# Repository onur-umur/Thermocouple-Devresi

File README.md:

# Thermocouple-Devresi
Jet Motoru için thermocouple devresi

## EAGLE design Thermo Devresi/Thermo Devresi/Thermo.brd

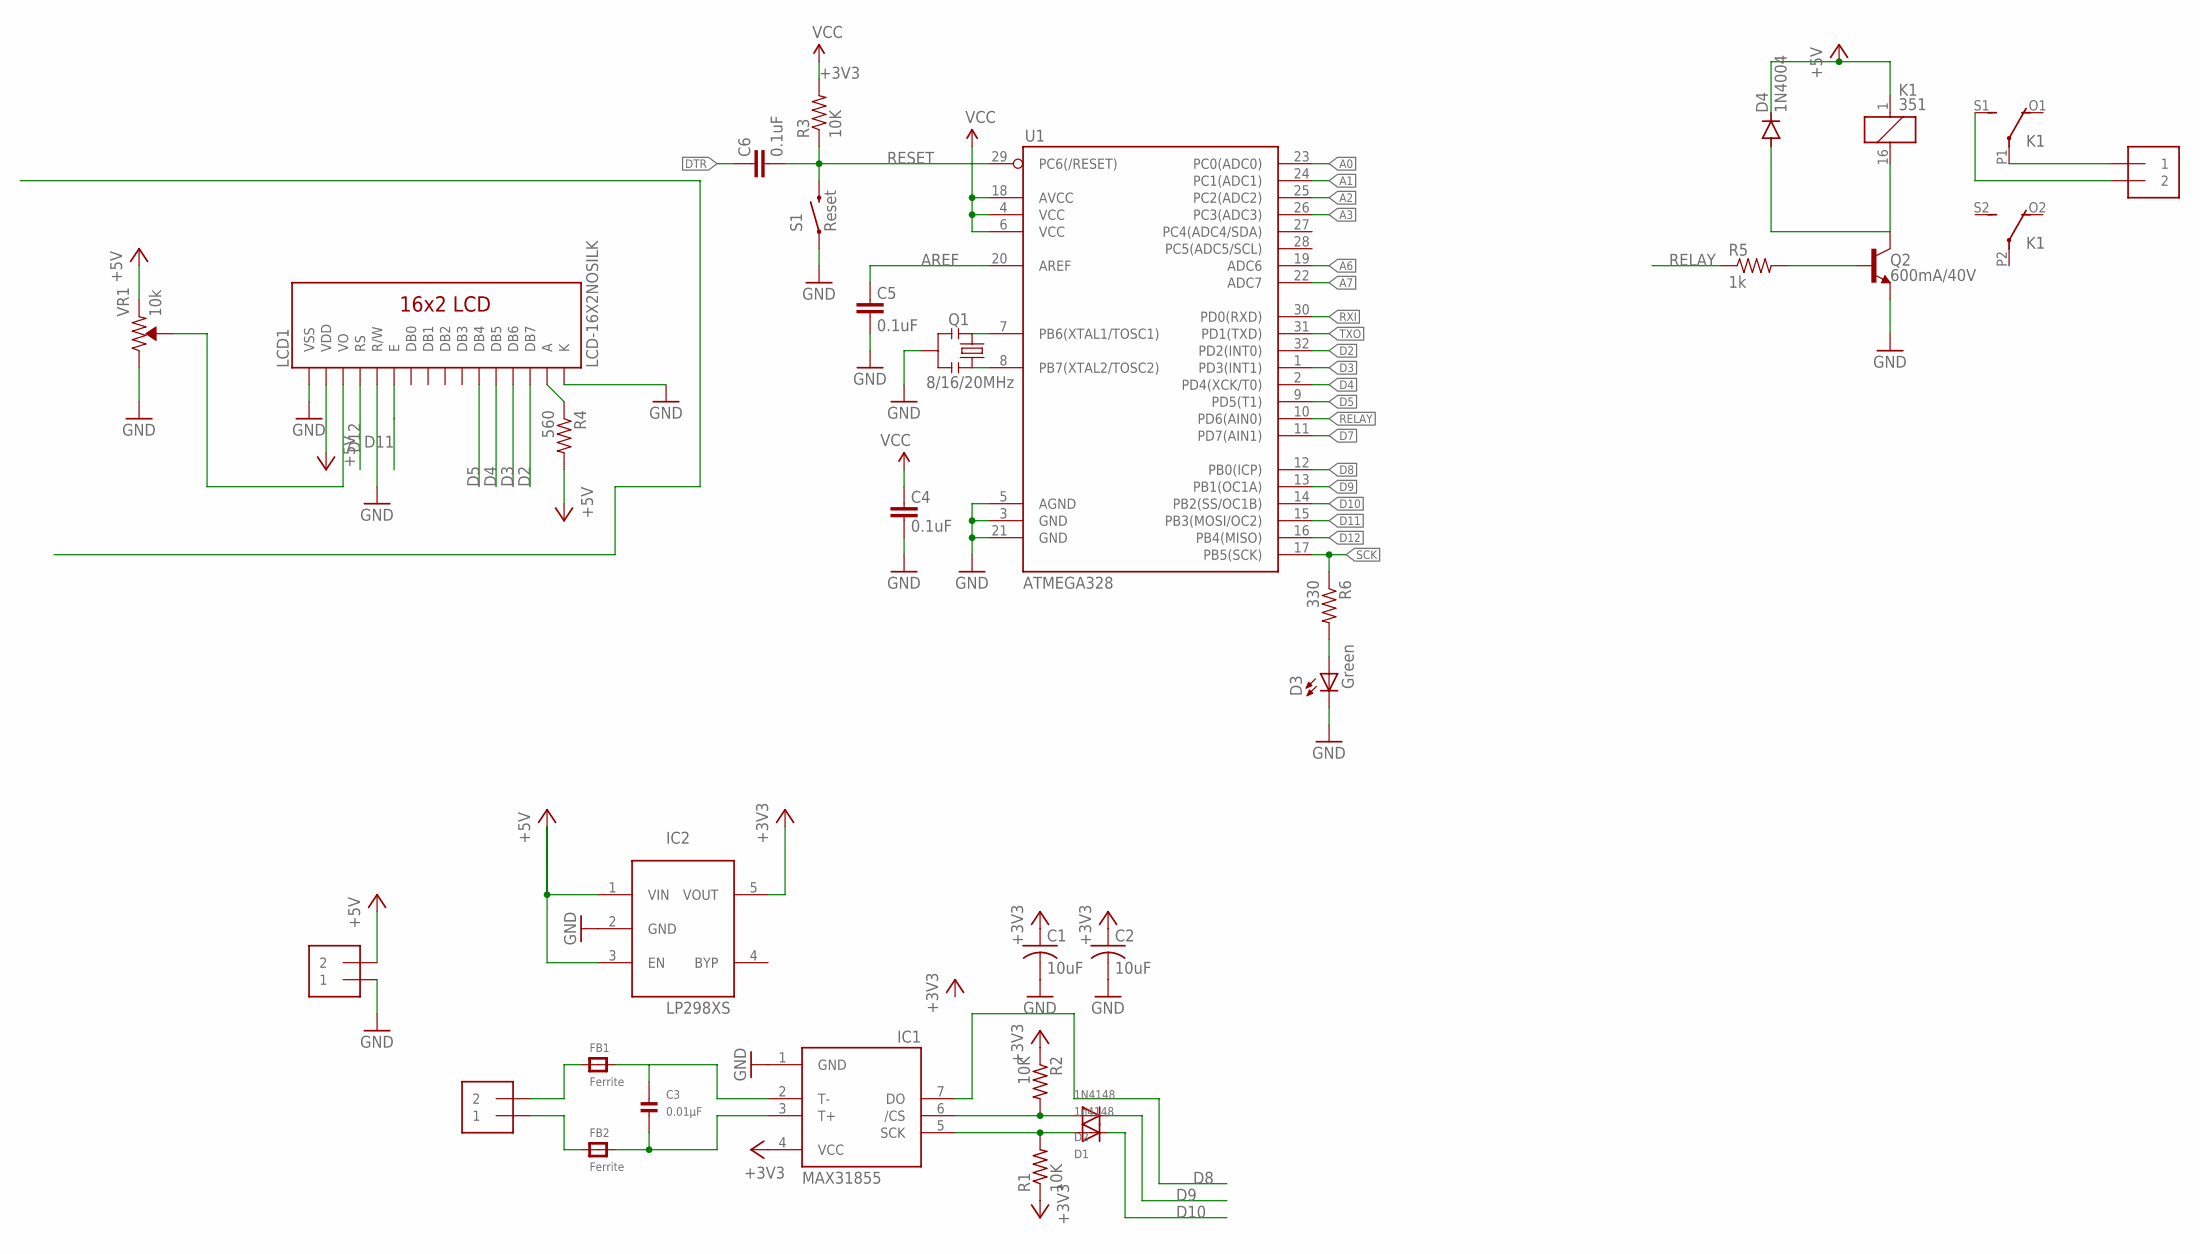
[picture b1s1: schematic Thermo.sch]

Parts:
C1, C2: 10uF; C0805K
C3: 0.01µF; _0805
C4, C5, C6: 0.1uF; 0603-CAP
D1: 1n4148; SOD-323F
D2: 1N4148; SOD-323F
D3: Green; 0603-LED-ALT1
D4: 1N4004; DO41-10
FB1, FB2: Ferrite; _0805
IC1: MAX31855; SO08
IC2: LP298XS; SOT23-5L
J1, J2, J3: 1X2-3.5MM
K1: 351
LCD1: LCD-16X2NOSILK; LCD-16X2_NOSILK
Q1: 8/16/20MHz; RESONATOR-SMD-1:1
Q2: 600mA/40V; SOT23-3
R1, R2: 10K; R0805
R3: 10K; 0805
R4: 560; 0805
R5: 1k; 0805
R6: 330; 0805
S1: Reset; TACTILE-SWITCH-SMD-ALT01
U1: ATMEGA328; TQFP32-08
VR1: 10k; TRIMPOT-SMD-3MM-CLOSED

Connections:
+3V3: C1.1, C2.1, IC1.4 (VCC), IC2.5 (VOUT), R1.1, R2.1, R3.2
+5V: D4.C, IC2.1 (VIN), IC2.3 (EN), J2.2, K1.1, LCD1.2 (VDD), R4.2, VR1.1 (CCW)
A0: U1.23 (PC0(ADC0))
A1: U1.24 (PC1(ADC1))
A2: U1.25 (PC2(ADC2))
A3: U1.26 (PC3(ADC3))
A6: U1.19 (ADC6)
A7: U1.22 (ADC7)
AREF: C5.2, U1.20 (AREF)
CS: D2.A, IC1.6 (/CS), R2.2
D2: LCD1.14 (DB7), U1.32 (PD2(INT0))
D3: LCD1.13 (DB6), U1.1 (PD3(INT1))
D4: LCD1.12 (DB5), U1.2 (PD4(XCK/T0))
D5: LCD1.11 (DB4), U1.9 (PD5(T1))
D7: U1.11 (PD7(AIN1))
D8: IC1.7 (DO), U1.12 (PB0(ICP))
D9: D2.C, U1.13 (PB1(OC1A))
D10: D1.C, U1.14 (PB2(SS/OC1B))
D11: LCD1.6 (E), U1.15 (PB3(MOSI/OC2))
D12: LCD1.4 (RS), U1.16 (PB4(MISO))
DTR: C6.2
GND: C1.2, C2.2, C4.1, C5.1, D3.C, IC1.1 (GND), IC2.2 (GND), J2.1, LCD1.1 (VSS), LCD1.5 (R/W), LCD1.16 (K), Q1.2, Q2.2 (E), S1.1, S1.2 (1), U1.3 (GND), U1.5 (AGND), U1.21 (GND), VR1.3 (CW)
unnamed: FB1.1, J1.2
unnamed: LCD1.15 (A), R4.1
unnamed: LCD1.3 (VO), VR1.2 (WIPER)
unnamed: C3.1, FB1.2, IC1.2 (T-)
unnamed: FB2.1, J1.1
unnamed: C3.2, FB2.2, IC1.3 (T+)
unnamed: D3.A, R6.2
unnamed: Q1.3, U1.8 (PB7(XTAL2/TOSC2))
unnamed: Q1.1, U1.7 (PB6(XTAL1/TOSC1))
unnamed: Q2.1 (B), R5.2
unnamed: D4.A, K1.16 (2), Q2.3 (C)
unnamed: J3.1, K1.P1
unnamed: J3.2, K1.S1 (S)
RELAY: R5.1, U1.10 (PD6(AIN0))
RESET: C6.1, R3.1, S1.3 (2), S1.4 (2), U1.29 (PC6(/RESET))
RXI: U1.30 (PD0(RXD))
SCK: D1.A, IC1.5 (SCK), R1.2, R6.1, U1.17 (PB5(SCK))
TXO: U1.31 (PD1(TXD))
VCC: C4.2, U1.4 (VCC), U1.6 (VCC), U1.18 (AVCC)

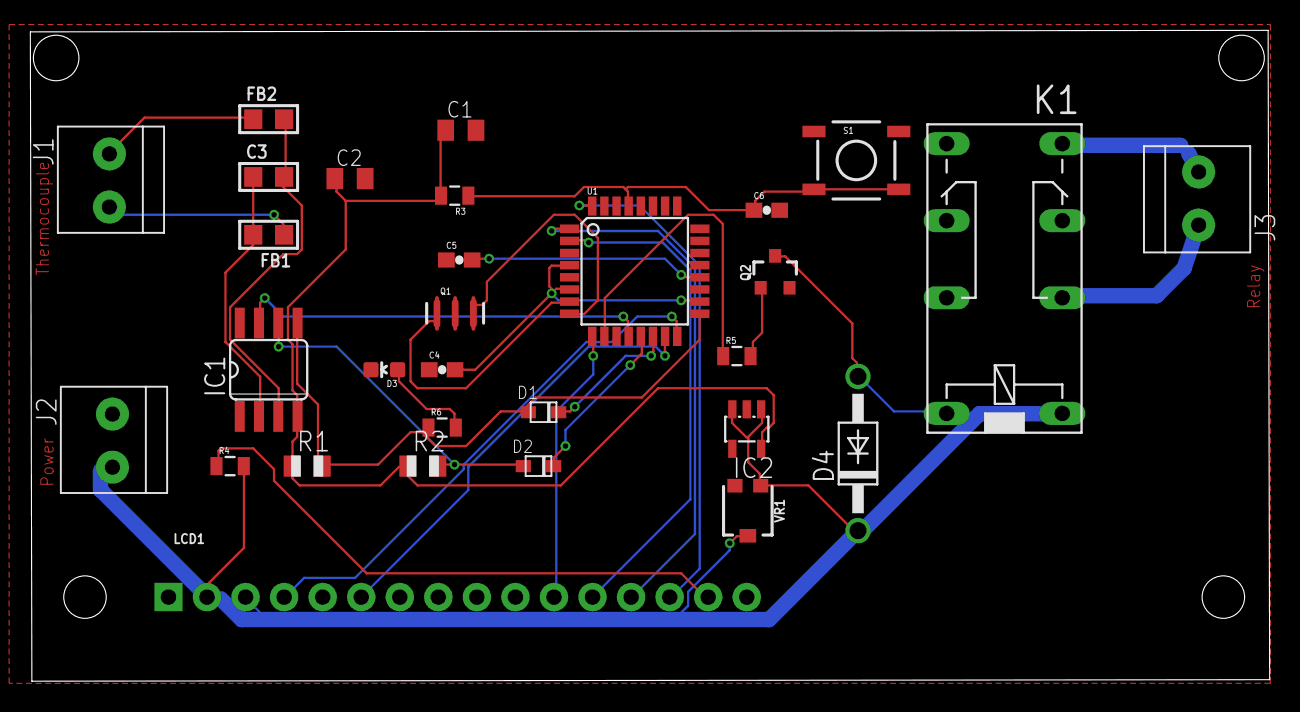
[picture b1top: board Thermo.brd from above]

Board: 2 copper layers, 81.6 x 42.9 mm, 30 parts (0 on the bottom side), 31 nets.

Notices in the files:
parts and their libraries:
SparkFun-Displays: Licensing: Creative Commons ShareAlike 4.0 International - https://creativecommons.org/licenses/by-sa/4.0
